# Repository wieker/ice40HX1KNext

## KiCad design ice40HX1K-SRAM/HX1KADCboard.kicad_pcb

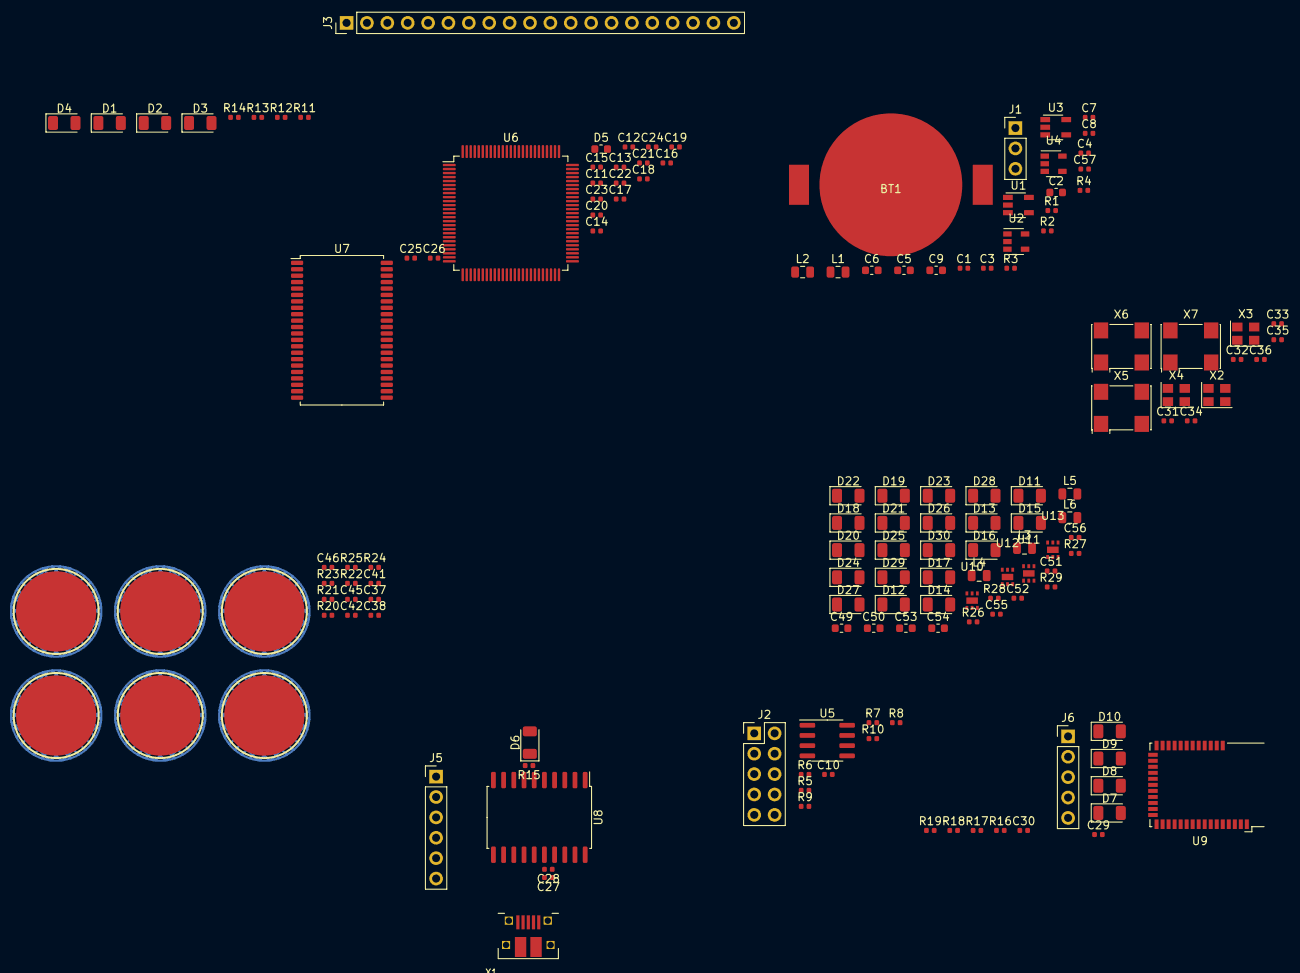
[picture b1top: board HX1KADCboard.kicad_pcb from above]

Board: 2 copper layers, 148 parts (0 on the bottom side), 136 nets, no tracks yet.

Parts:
BT1: Battery_Cell; CR2032
C1, C3, C27, C29: 4.7uF; C_0402_1005Metric
C2, C5, C6, C9, C49, C50, C53, C54: 10uF; C_0603_1608Metric
C4, C7, C8, C10, C11, C12, C13, C14, C15, C16, C17, C18, C19, C20, C21, C22, C23, C24, C25, C26, C28, C30, C57: 0.1uF; C_0402_1005Metric
C31, C32, C33, C34, C35, C36: 0.01uF; C_0402_1005Metric
C37, C38, C41, C42, C45, C46: 100pF; C_0402_1005Metric
C39, C40, C43, C44, C47, C48: Ccap; CAPBUTTON
C51, C52, C55, C56: 1uF; C_0402_1005Metric
D1, D2, D3, D4, D6, D7, D8, D9, D10, D11, D12, D13, D14, D15, D16, D17, D18, D19, D20, D21, D22, D23, D24, D25, D26, D27, D28, D29, D30: LED; LED_1206_3216Metric
D5: CDBU05; C_0603_1608Metric
J1: Conn_01x03_Male; PinHeader_1x03_P2.54mm_Vertical
J2: Conn_02x05_Odd_Even; PinHeader_2x05_P2.54mm_Vertical
J3: Conn_01x20_Male; PinHeader_1x20_P2.54mm_Vertical
J5: Conn_01x06_Male; PinHeader_1x06_P2.54mm_Vertical
J6: Conn_01x05; PinHeader_1x05_P2.54mm_Vertical
L1, L2: 2.2uH; L_0805_2012Metric
L3, L4, L5, L6: 10uH; L_0805_2012Metric
R1, R2, R3, R20, R21, R22, R23, R24, R25: 100kOhm; R_0402_1005Metric
R4: 450kOhm; R_0402_1005Metric
R5, R6, R7, R8, R9, R10, R15, R16, R17, R18, R19: 10kOhm; R_0402_1005Metric
R11, R12, R13, R14: 10kohm; R_0402_1005Metric
R26, R27, R28, R29: 20Ohm; R_0402_1005Metric
U1, U3: LTC3406ES5; TSOT-23-5
U2, U4: MAX40200AUK; SOT-23-5
U5: AT25SF081-SSHD-X; SOIC-8_3.9x4.9mm_P1.27mm
U6: ICE40HX1K-VQ100(VQFP100); LQFP-100_14x14mm_P0.5mm
U7: AS7C34096A; TSOP-II-44_10.16x18.41mm_P0.8mm
U8: ATSAMD11D14A-SS; SOIC-20W_7.5x12.8mm_P1.27mm
U9: BL652; Laird_BL652
U10, U11, U12, U13: FAN5341
X1: USBFCI_10103594_MILL; FCI_10103594_MILL
X2, X3, X4: ASE-10MHz; Oscillator_SMD_Abracon_ASE-4Pin_3.2x2.5mm
X5, X6, X7: ASV-xxxMHz; Oscillator_SMD_Abracon_ASV-4Pin_7.0x5.1mm

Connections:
+1V2: C2.1, C11.1, C13.1, C23.1, C24.1, J1.3, L1.1, R2.2, U6.11, U6.35, U6.61, U6.77
+3V3: C1.1, C4.1, C5.1, C8.1, C9.1, C10.1, C12.1, C14.1, C15.1, C16.1, C17.1, C18.1, C19.1, C20.1, C21.1, C22.1, C25.2, C26.2, C27.1, C28.1, C29.1, C30.1, C31.1, C32.1, C33.1, C34.1, C35.1, C36.1, C49.1, C50.1, C53.1, C54.1, D5.2, J1.2, J2.1, J3.1, J3.8, J3.20, J5.5, J5.6, J6.1, J6.2, L3.1, L4.1, L5.1, L6.1, R5.1, R6.1, R7.1, R8.1, R9.1, R10.1, R20.1, R21.1, R22.1, R23.1, R24.1, R25.1, U1.1, U1.4, U2.5, U4.5, U5.3, U5.7, U5.8, U6.6, U6.14, U6.22, U6.31, U6.38, U6.50, U6.58, U6.67, U6.88, U6.92, U7.11, U7.33, U8.17, U9.26, U10.2, U11.2, U12.2, U13.2, X2.1, X2.4, X3.1, X3.4, X4.1, X4.4, X5.1, X5.4, X6.1, X6.4, X7.1, X7.4
+5V: C3.1, U3.1, U3.4, X1.VBUS
CDONE: D1.2, J2.5, R5.2, U6.43, U8.18, U9.36
CRESET: J2.7, R6.2, U6.44, U8.19, U9.37
GND: BT1.2, C1.2, C2.2, C3.2, C4.2, C5.2, C6.2, C7.2, C8.2, C9.2, C10.2, C11.2, C12.2, C13.2, C14.2, C15.2, C16.2, C17.2, C18.2, C19.2, C20.2, C21.2, C22.2, C23.2, C24.2, C25.1, C26.1, C27.2, C28.2, C29.2, C30.2, C31.2, C32.2, C33.2, C34.2, C35.2, C36.2, C37.2, C38.2, C39.2, C40.2, C41.2, C42.2, C43.2, C44.2, C45.2, C46.2, C47.2, C48.2, C49.2, C50.2, C51.2, C52.2, C53.2, C54.2, C55.2, C56.2, C57.2, D6.1, D7.1, D8.1, D9.1, D10.1, J1.1, J2.2, J3.2, J3.9, J3.15, J3.19, J5.1, J6.5, R1.2, R3.2, R11.1, R12.1, R13.1, R14.1, R26.2, R27.2, R28.2, R29.2, U1.2, U2.2, U3.2, U4.2, U5.4, U6.5, U6.17, U6.23, U6.32, U6.39, U6.47, U6.55, U6.70, U6.84, U6.98, U7.12, U7.34, U8.16, U9.1, U9.16, U9.27, U9.39, U10.6, U11.6, U12.6, U13.6, X1.BASE@1, X1.BASE@2, X1.GND, X1.SPRT@1, X1.SPRT@2, X1.SPRT@3, X1.SPRT@4, X2.2, X3.2, X4.2, X5.2, X6.2, X7.2
IO1: U6.1, U7.27
IO2: U6.2, U7.26
IO3: U6.3, U7.20
IO4: U6.4, U7.19
IO7: U6.7, U7.18
IO8: U6.8, U7.17
IO9: U6.9, U7.16
IO10: U6.10, U7.15
IO12: U6.12, U7.14
IO13: U6.13, U7.13
IO15: U6.15, U7.10
IO16: U6.16, U7.9
IO18: U6.18, U7.8
IO19: U6.19, U7.7
IO20: U6.20, U7.6
IO21: U6.21, U7.5
IO24: U6.24, U7.4
IO25: U6.25, U7.3
IO26: U6.26, U7.41
IO27: U6.27, U7.40
IO28: U6.28, U7.39
IO29: U6.29, U7.38
IO30: U6.30, U7.37
IO33: U6.33, U7.36
IO34: U6.34, U7.35
IO36: U6.36, U7.32
IO37: U6.37, U7.31
IO40: U6.40, U7.30
IO41: U6.41, U7.29
IO43: U6.42, U7.28
IO51: D4.2, U6.51
IO52: D3.2, U6.52
IO53: D2.2, U6.53
IO54: U6.54, U8.5
IO56: U6.56, U8.4
IO57: U6.57, U9.15
IO59: U6.59, U9.17
IO60: U6.60, U8.8
IO62: U6.62, X3.3
IO63: U6.63, X5.3
IO64: U6.64, U8.7
IO65: U6.65, X2.3
IO66: U6.66, X4.3
IO68: U6.68, X6.3
IO69: U6.69, X7.3
IO71: U6.71, U12.3
IO72: U6.72, U13.3
IO73: U6.73, U10.3
IO74: U6.74, U11.3
IO78: J3.18, U6.78
IO79: J3.17, U6.79
IO80: J3.16, U6.80
IO81: J3.14, U6.81
IO82: J3.13, U6.82
IO83: J3.12, U6.83
IO85: J3.11, U6.85
IO86: J3.10, U6.86
IO87: J3.7, U6.87
IO89: J3.6, U6.89
IO90: J3.5, U6.90
IO91: J3.4, U6.91
IO93: J3.3, U6.93
IO94: C45.1, C47.1, R24.2, U6.94
IO95: C41.1, C43.1, R22.2, U6.95
IO96: C37.1, C39.1, R20.2, U6.96
IO97: C46.1, C48.1, R25.2, U6.97
IO99: C42.1, C44.1, R23.2, U6.99
IO100: C38.1, C40.1, R21.2, U6.100
unnamed: BT1.1, C57.1, U2.1, U2.3
unnamed: C6.1, C7.1, L2.1, R4.2, U4.1, U4.3
unnamed: C51.1, D11.2, U10.1
unnamed: C52.1, D12.2, U11.1
unnamed: C55.1, D21.2, U12.1
unnamed: C56.1, D22.2, U13.1
unnamed: D1.1, R11.2
unnamed: D2.1, R12.2
unnamed: D3.1, R13.2
unnamed: D4.1, R14.2
unnamed: D5.1, U6.75
unnamed: D6.2, R15.2
unnamed: D7.2, R16.2
unnamed: D8.2, R17.2
unnamed: D9.2, R18.2
unnamed: D10.2, R19.2
unnamed: D11.1, D13.2
unnamed: D12.1, D14.2
unnamed: D13.1, D15.2
unnamed: D14.1, D16.2
unnamed: D15.1, D17.2
unnamed: D16.1, D18.2
unnamed: D17.1, D19.2
unnamed: D18.1, D20.2
unnamed: D19.1, R26.1, U10.4
unnamed: D20.1, R27.1, U11.4
unnamed: D21.1, D23.2
unnamed: D22.1, D24.2
unnamed: D23.1, D25.2
unnamed: D24.1, D26.2
unnamed: D25.1, D27.2
unnamed: D26.1, D28.2
unnamed: D27.1, D29.2
unnamed: D28.1, D30.2
unnamed: D29.1, R28.1, U12.4
unnamed: D30.1, R29.1, U13.4
unnamed: J6.3, U9.6
unnamed: J6.4, U9.5
unnamed: L1.2, U1.3
unnamed: L2.2, U3.3
unnamed: L3.2, U10.5
unnamed: L4.2, U11.5
unnamed: L5.2, U12.5
unnamed: L6.2, U13.5
unnamed: R1.1, R2.1, U1.5
unnamed: R3.1, R4.1, U3.5
unnamed: R16.1, U9.28
unnamed: R17.1, U9.11
unnamed: R18.1, U9.29
unnamed: R19.1, U9.10
unnamed: U8.14, X1.D-
unnamed: U8.15, X1.D+
SPI_CS: J2.6, R10.2, U5.1, U6.49, U8.1, U9.2
SPI_IN: J2.9, R7.2, U5.2, U6.46, U8.2, U9.3
SPI_OUT: J2.10, R8.2, U5.5, U6.45, U8.3, U9.4
SPI_SCK: J2.8, R9.2, U5.6, U6.48, U8.20, U9.38
led_mcu: R15.1, U8.6
nrf_rx: U8.9, U9.31
nrf_tx: U8.10, U9.9
swd_clk: J5.4, U8.12
swd_io: J5.3, U8.13
swd_rst: J5.2, U8.11

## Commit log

2020-03-01 ice40HX1K fpga + AS7C34096A SRAM
2020-03-03 Started USB => ice40 HX1K Bridge with ATSAMD11C14A
2020-03-04 add MAX40203 in power supply of the ice40 ice40HX1K fpga to OR supply USB/battery cell
2020-03-07 add nRF52 module for FPGA programming
2020-03-07 add ASE-10.000MHZ XTAL
2020-03-07 add XTAL
2020-03-07 add FAN5341 + touch buttons
2020-03-07 wiring FPGA nRF52 and ATSAMD11
2020-03-08 wiring FPGA
2020-03-08 starting layout
2020-03-08 starting AutoRoute
2020-03-08 starting AutoRoute - fail
2020-03-08 Generated gerber
2020-03-08 Generated gerber v2
2020-04-04 fpgaNext-2
